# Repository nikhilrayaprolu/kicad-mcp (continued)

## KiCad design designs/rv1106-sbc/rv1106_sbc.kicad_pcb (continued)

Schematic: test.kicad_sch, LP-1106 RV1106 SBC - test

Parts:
TP1: VSYS; TestPoint_Pad_D1.0mm
TP2: 3V3; TestPoint_Pad_D1.0mm
TP3: 1V8; TestPoint_Pad_D1.0mm
TP4: VDDR; TestPoint_Pad_D1.0mm
TP5: 0V9; TestPoint_Pad_D1.0mm
TP6: GND; TestPoint_Pad_D1.0mm
TP7: VBUS; TestPoint_Pad_D1.0mm

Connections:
GND: TP6.1; also elsewhere on the board
VBUS: TP7.1; also elsewhere on the board
VCC_1V8: TP3.1; also elsewhere on the board
VCC_3V3: TP2.1; also elsewhere on the board
VCC_DDR: TP4.1; also elsewhere on the board
VDD_0V9: TP5.1; also elsewhere on the board
VSYS: TP1.1; also elsewhere on the board

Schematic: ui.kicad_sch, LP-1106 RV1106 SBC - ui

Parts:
C57: 1n; C_0402_1005Metric
D3: blue; LED_0603_1608Metric
R22, R23: 100R; R_0402_1005Metric
R24: 10k; R_0402_1005Metric
R28: 1k; R_0402_1005Metric
SW1, SW2: TS-1187A; SW_Push_1P1T_XKB_TS-1187A; MPN TS-1187A-B-A-B; LCSC C318884

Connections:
GND: C57.2, D3.1 (K), SW1.2, SW2.2; also elsewhere on the board
LED_LED_STATUS_A: D3.2 (A), R28.2
LED_STATUS: R28.1; also elsewhere on the board
NPOR: R22.1; also elsewhere on the board
NPOR_BTN: R22.2, SW1.1
RECOVERY: C57.1, R23.1, R24.2; also elsewhere on the board
RECOVERY_BTN: R23.2, SW2.1
VCC_1V8: R24.1; also elsewhere on the board

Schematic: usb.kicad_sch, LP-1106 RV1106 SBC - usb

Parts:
C59: 100n; C_0402_1005Metric
R26: 10k; R_0402_1005Metric
R27: 18k; R_0402_1005Metric

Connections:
GND: C59.2, R27.2; also elsewhere on the board
USB_VBUSDET: C59.1, R26.2, R27.1; also elsewhere on the board
VBUS: R26.1; also elsewhere on the board

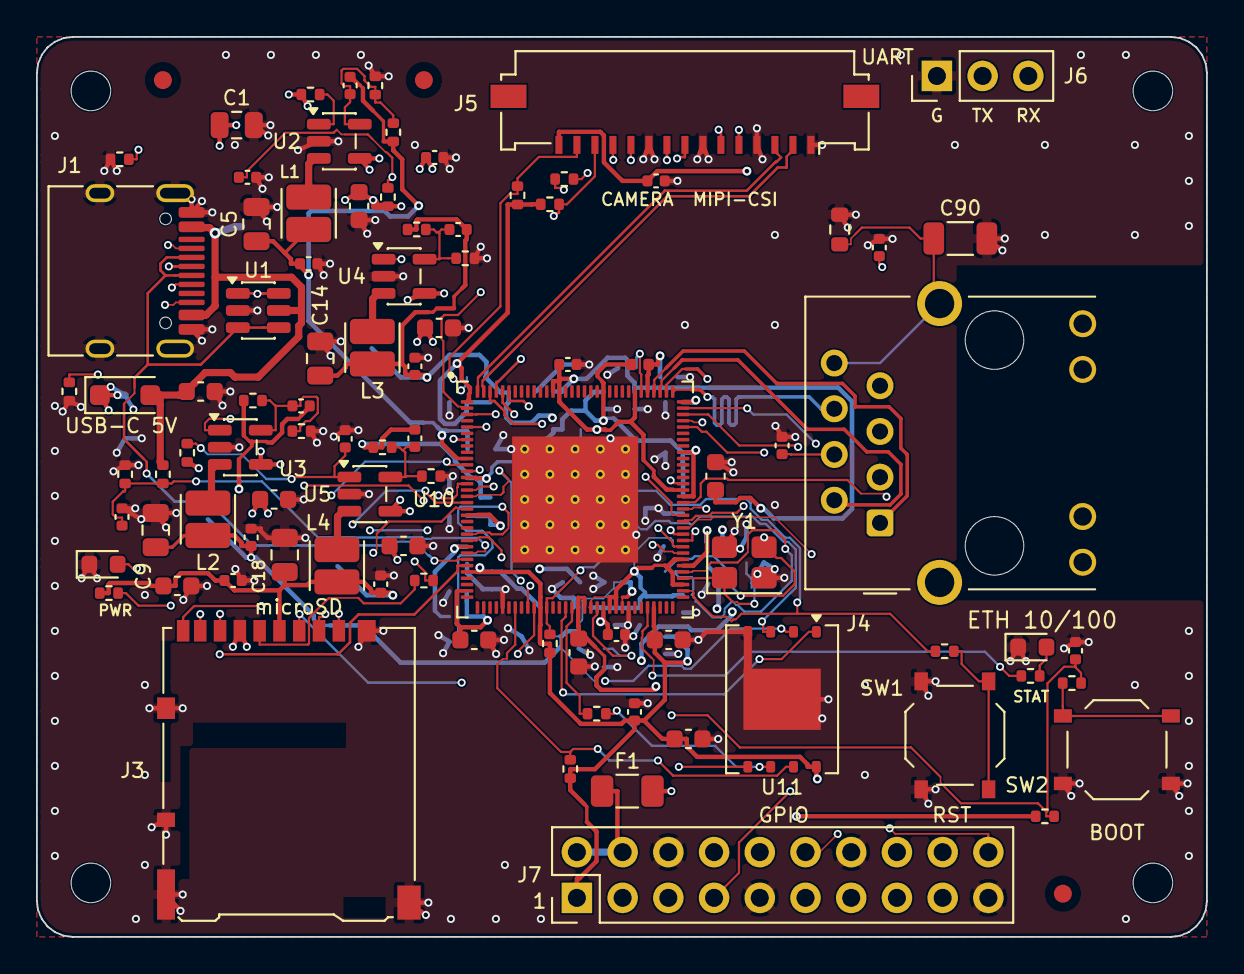
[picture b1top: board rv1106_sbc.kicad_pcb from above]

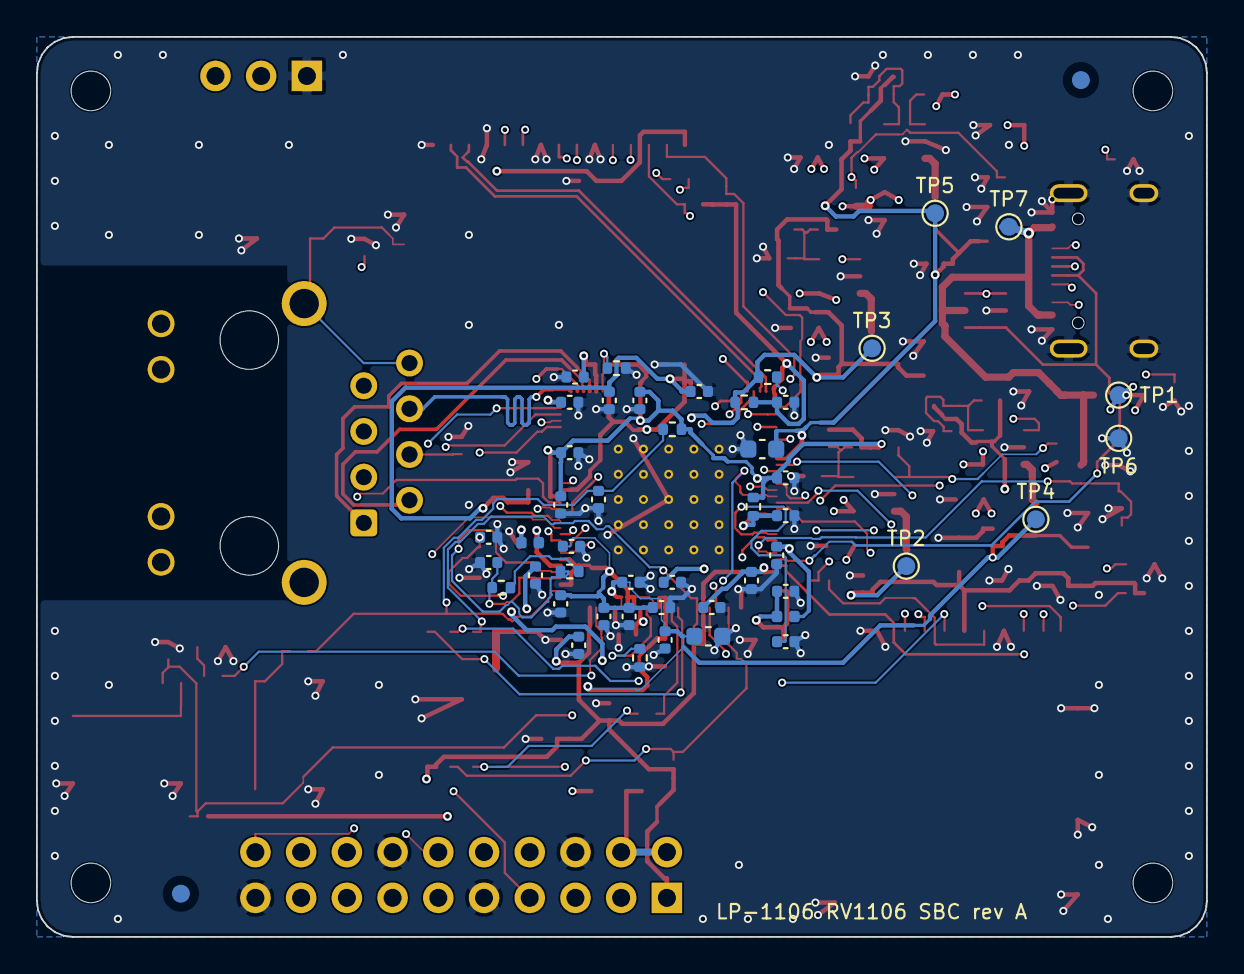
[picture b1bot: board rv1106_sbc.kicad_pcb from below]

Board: 4 copper layers, 65.0 x 50.0 mm, 146 parts (49 on the bottom side), 89 nets.

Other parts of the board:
FID1, FID2, FID3, FID4, FID5: Fiducial; Fiducial_1mm_Mask2mm
H1, H2, H3, H4: MountingHole; MountingHole_2.2mm_M2

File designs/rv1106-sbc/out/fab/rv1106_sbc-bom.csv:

Comment,Designator,Footprint,Quantity,MPN,LCSC Part #
22u/10V,"C1,C14,C18,C5,C9",C_0805_2012Metric,5,,
100n,"C10,C12,C15,C19,C2,C26,C27,C28,C29,C30,C31,C35,C37,C38,C39,C40,C42,C43,C45,C46,C47,C48,C49,C50,C51,C52,C59,C6,C61,C63",C_0402_1005Metric,30,,
1u,"C21,C24,C25,C34,C36,C53,C91",C_0402_1005Metric,7,,
10u,"C22,C23,C32,C33,C41,C44,C60,C62",C_0603_1608Metric,8,,
2.2u/10V,C3,C_0603_1608Metric,1,,
10u/10V,"C13,C17,C4,C8",C_0603_1608Metric,4,,
18p,"C54,C55",C_0402_1005Metric,2,,
10n,"C56,C64,C65",C_0402_1005Metric,3,,
1n,"C57,C58",C_0402_1005Metric,2,,
22p,"C11,C16,C20,C7",C_0402_1005Metric,4,,
1n/2kV,C90,C_1206_3216Metric,1,,
MBR230LSFT1G,D1,D_SOD-123F,1,MBR230LSFT1G,
green,D2,LED_0603_1608Metric,1,,
blue,D3,LED_0603_1608Metric,1,,
0.5A PTC,F1,Fuse_1206_3216Metric,1,SMD1206P050TF,
120R@100MHz,"FB1,FB2,FB3",L_0402_1005Metric,3,BLM15PD121SN1D,
TYPE-C-31-M-12,J1,USB_C_Receptacle_HRO_TYPE-C-31-M-12,1,TYPE-C-31-M-12,C165948
DM3AT-SF-PEJM5,J3,microSD_HC_Hirose_DM3AT-SF-PEJM5,1,DM3AT-SF-PEJM5,
HR911105A,J4,RJ45_Hanrun_HR911105A_Horizontal,1,HR911105A,C12074
FPC 15P 1.0mm,J5,Molex_200528-0150_1x15-1MP_P1.00mm_Horizontal,1,,
DEBUG UART,J6,PinHeader_1x03_P2.54mm_Vertical,1,,
GPIO 2x10,J7,PinHeader_2x10_P2.54mm_Vertical,1,,
1uH,L1,L_Cenker_CKCS252012,1,CKCS252012,
2.2uH,"L2,L3,L4",L_Cenker_CKCS252012,3,CKCS252012,
5.1k,"R1,R2",R_0402_1005Metric,2,,
453k 1%,R11,R_0402_1005Metric,1,,
200k,R13,R_0402_1005Metric,1,,
2.2k,R14,R_0402_1005Metric,1,,
1R,R15,R_0402_1005Metric,1,,
100R,"R16,R22,R23",R_0402_1005Metric,3,,
240R 1%,R17,R_0402_1005Metric,1,,
6.04k 1%,R18,R_0402_1005Metric,1,,
22R,"R19,R29,R32,R34",R_0402_1005Metric,4,,
1M,R20,R_0402_1005Metric,1,,
1k,"R21,R28",R_0402_1005Metric,2,,
18k,R27,R_0402_1005Metric,1,,
49.9k 1%,R3,R_0402_1005Metric,1,,
1M,R33,R_0603_1608Metric,1,,
4.7k,"R35,R36",R_0402_1005Metric,2,,
100k 1%,"R10,R12,R4,R7",R_0402_1005Metric,4,,
10k,"R24,R25,R26,R30,R31,R5",R_0402_1005Metric,6,,
124k 1%,R6,R_0402_1005Metric,1,,
100k,R8,R_0402_1005Metric,1,,
200k 1%,R9,R_0402_1005Metric,1,,
TS-1187A,"SW1,SW2",SW_Push_1P1T_XKB_TS-1187A,2,TS-1187A-B-A-B,C318884
VSYS,TP1,TestPoint_Pad_D1.0mm,1,,
3V3,TP2,TestPoint_Pad_D1.0mm,1,,
1V8,TP3,TestPoint_Pad_D1.0mm,1,,
VDDR,TP4,TestPoint_Pad_D1.0mm,1,,
0V9,TP5,TestPoint_Pad_D1.0mm,1,,
GND,TP6,TestPoint_Pad_D1.0mm,1,,
USBLC6-2SC6,U1,SOT-23-6,1,USBLC6-2SC6,C7519
RV1106G3,U10,QFN-128-1EP_12.3x12.3mm_P0.35mm_EP7x7mm,1,RV1106G3,
W25N01GVZEIG,U11,WSON-8-1EP_8x6mm_P1.27mm_EP3.4x4.3mm,1,W25N01GVZEIG,C111706
TLV62569DBV,"U2,U3,U4,U5",SOT-23-5,4,TLV62569DBVR,C141836
24MHz,Y1,Crystal_SMD_3225-4Pin_3.2x2.5mm,1,,

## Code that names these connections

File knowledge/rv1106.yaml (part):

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      - {pin: 81, name: GPIO1_VCC3V3, range_V: [3.0, 3.465], note: "3.3 V only; VCCIO1 domain (pins 72-80)", reference: "VCC_3V3, C39 100nF", src: "Rockchip_RV1106_Datasheet_V2.2-20260602.pdf#p26; Luckfox-Pico-Pro-Max.pdf#p1"}
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      - {pin: 28, name: USB_AVDD3V3, range_V: [3.0, 3.6], reference: "VCC_3V3 direct, C9 100nF", src: "Rockchip_RV1106_Datasheet_V2.2-20260602.pdf#p26; Luckfox-Pico-Pro-Max.pdf#p1"}
      - {pin: 101, name: ETH_AVDD3V3, range_V: [2.97, 3.63], reference: "net FEPHY_AVDD3V3 = VCC_3V3 via FB1 (UPZ1005D121-1R3TF / BLM15PD121SN1 printed), C8 100nF", src: "Rockchip_RV1106_Datasheet_V2.2-20260602.pdf#p26; Luckfox-Pico-Pro-Max.pdf#p1 @230-254,526-538"}
      - {pin: 13, name: GPIO4_VCC, range_V_3v3: [3.0, 3.465], range_V_1v8: [1.62, 1.98], note: "VCCIO4 = SDMMC0 domain (pins 11,12,14-18)", reference: "VCC_3V3, C41 100nF", src: "Rockchip_RV1106_Datasheet_V2.2-20260602.pdf#p26; Luckfox-Pico-Pro-Max.pdf#p1"}
      - {pin: 43, name: GPIO3_VCC, note: "VCCIO3 = EMMC/FSPI domain (pins 38-42,44-48)", reference: "net VCCIO_FLASH = VCC_3V3, C40 100nF (+C42 10uF/C43 100nF at flash)", src: "Rockchip_RV1106_Datasheet_V2.2-20260602.pdf#p26; Luckfox-Pico-Pro-Max.pdf#p1"}
      - {pin: 88, name: GPIO6_VCC, note: "VCCIO6 domain (pins 83-87,89-95)", reference: "VCC_3V3", src: "Rockchip_RV1106_Datasheet_V2.2-20260602.pdf#p26; Luckfox-Pico-Pro-Max.pdf#p1"}
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      Luckfox SCH labels the VDD_0V9 buck "Setp 1" (EN pulled up with 10K, no cap -> starts first); VCC_DDR and VCC_1V8 share
      enable net VCC_DDR_1V8_EN with 200K/100nF RC delay (Ultra-W labels this block "VCC_DDR--->VCC_1V8 Setp 2");
      VCC_3V3 EN via 200K/100nF from PWR_EN. Practical order: 0.9 V -> 1.35 V/1.8 V -> 3.3 V.
    reset: "nPOR (pin 66) pulled up to VCC_3V3 by R12 1K with C38 10nF to GND (RC power-on reset); reset key Key1 via R22 100R."
    src: "Luckfox-Pico-Pro-Max.pdf#p1 @222-556,6-64; Luckfox-Pico-Ultra-W.pdf#p1 @585-745,205-305; Luckfox-Pico-Pro-Max.pdf#p1 @445-535,180-230"
    unverified: true    # Rockchip's own sequencing rule is in the (non-public here) hardware design guide

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    reference: "Y2 32.768 kHz passive crystal 2012; C33 18pF, C34 18pF C0G. Optional (RTC)."
    src: "Luckfox-Pico-Pro-Max.pdf#p1 @388-412,161-177"
  reset:
    pins: {nPOR: 66}                                # src: Rockchip_RV1106_Datasheet_V2.2-20260602.pdf#p21
    reference: "Active-low. R12 1K pull-up to VCC_3V3, C38 10nF to GND; Key1 to GND via R22 100R; ED1 ESD (NC/ESD5451N)."
    src: "Luckfox-Pico-Pro-Max.pdf#p1 @406,224 (R12/C38) and @530-622,400-440 (Key1)"
  recovery_maskrom:
    pins: {SARADC_IN0: 23}
    reference: >-
      Net RECOVERY on SARADC_IN0 (pin 23): R21 10K pull-up to VCC_1V8, C44 1nF to GND, Key2 ("RECOVERY Key") to GND via
      R23 100R (ED2 ESD NC). Holding it low at power-up is the BOOT/recovery button.
    behaviour: >-
      Rockchip convention: SARADC_IN0 low at boot -> loader/maskrom (USB download via rkdeveloptool/upgrade_tool on USB OTG).
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    src: "Luckfox-Pico-Pro-Max.pdf#p1 @445-535,365-440; Rockchip_RV1106_Datasheet_V2.2-20260602.pdf#p7"
    unverified: true
  fspi_spi_nand:
    pins: {FSPI_CLK: 48, FSPI_CS0: 47, FSPI_D0: 41, FSPI_D1: 42, FSPI_D2: 44, FSPI_D3: 39}   # src: Rockchip_RV1106_Datasheet_V2.2-20260602.pdf#p22
    io_domain: "VCCIO3 = pin 43 GPIO3_VCC (VCCIO_FLASH = 3.3 V in reference)"
    reference: >-
      U2 Winbond W25N02KVZEIR (2Gb SPI NAND, WSON-8 + EPAD): pin1 /CS=FSPI_CS0N, 2 DO(IO1)=FSPI_D1, 3 /WP(IO2)=FSPI_D2,
      4 VSS, 5 DI(IO0)=FSPI_D0, 6 CLK=FSPI_CLK, 7 /HOLD(IO3)=FSPI_D3, 8 VCC=VCCIO_FLASH, 9 EPAD=GND.
      FSPI_CLK has R15 22R series resistor at the SoC. R18 10K pull-up on FSPI_D2, R19 10K pull-up on FSPI_D3 (to VCCIO_FLASH).
      VCCIO_FLASH decoupling C42 10uF + C43 100nF.
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    conflict: "Pins 12/14 are also UART2_TX_M0/UART2_RX_M0, so the debug console uses UART2_M1 instead."
    src: "Rockchip_RV1106_Datasheet_V2.2-20260602.pdf#p21; Luckfox-Pico-Pro-Max.pdf#p1 @445-622,440-505 and @540-622,195-240"
  usb2_otg:
    pins: {USB_DP: 27, USB_DM: 26, USB_VBUSDET: 25}   # src: Rockchip_RV1106_Datasheet_V2.2-20260602.pdf#p22
    supplies: {USB_AVDD3V3: 28, SARADC_USB_AVDD1V8: 24}
    id_pin: "None on QFN128 (no USB_ID in DS Table 2-1); host/device role is set in software."
    external_resistors: "None on the QFN part: there is no USB reference-resistor pin."
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  uart2_debug_console:
    pins: {UART2_TX_M1: 79, UART2_RX_M1: 80}         # GPIO1_B2 / GPIO1_B3; src: Rockchip_RV1106_Datasheet_V2.2-20260602.pdf#p21
    io_domain: "VCCIO1 (3.3 V only)"
    reference: "Pins 79/80 -> nets UART2_TX/UART2_RX -> header GP00/GP01 (U3 40-pin). Luckfox Linux console is UART2_M1, 115200 8N1."
    src: "Rockchip_RV1106_Datasheet_V2.2-20260602.pdf#p21; Luckfox-Pico-Pro-Max.pdf#p1 @222-395,62-118 and @325-385,190-262"
    console_baud_unverified: true
  saradc:
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  required_external_resistors_summary:
    - {pin: 102, name: ETH_EXTR, value: "6.04K 1% to GND", src: "Luckfox-Pico-Pro-Max.pdf#p1"}
    - {pin: 52, name: DRAM_ZQ, value: "240R 1% to GND", src: "Luckfox-Pico-Pro-Max.pdf#p1"}
    - {pin: 66, name: nPOR, value: "1K pull-up to 3V3 + 10nF to GND", src: "Luckfox-Pico-Pro-Max.pdf#p1"}
    - {pin: 23, name: SARADC_IN0, value: "10K pull-up to 1V8 + 1nF (recovery key)", src: "Luckfox-Pico-Pro-Max.pdf#p1"}
    - {pins: [68, 69], name: OSC, value: "1M across XIN/XOUT, 22R series on XOUT, 2x18pF", src: "Luckfox-Pico-Pro-Max.pdf#p1"}
  datasheet_name_quirks:
    - {pin: 110, note: "DS prints 'SDMMC_D0/I2S0_LRCK/...'; by analogy with pins 109/111-114 this is SDMMC1_D0_M0 (SCH shows SDIO_D0_M0).", src: "Rockchip_RV1106_Datasheet_V2.2-20260602.pdf#p22; Luckfox-Pico-Pro-Max.pdf#p1", unverified: true}
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  - {ref: U5, part: unknown, role: "buck 5V -> VCC_1V8, 1.0uH", src: "Luckfox-Pico-Pro-Max.pdf#p1", unverified: true}
  - {ref: U7, part: unknown, role: "buck 5V -> VCC_DDR 1.35V, 1.0uH", src: "Luckfox-Pico-Pro-Max.pdf#p1", unverified: true}
  - {ref: U6, part: unknown, role: "buck 5V -> VCC_3V3 with BST cap, 2.2uH, FB 0.8V", src: "Luckfox-Pico-Pro-Max.pdf#p1", unverified: true}
  - {ref: U3, part: "40-pin header (Pico/RP2040-style GP00..GP28, VBUS, VSYS, 3V3_En, 3V3_Out, Vref, RUN=NPOR)", role: "IO header", src: "Luckfox-Pico-Pro-Max.pdf#p1 @222-395,62-118"}
  - {ref: D1, part: MBR230LSFT1G, role: "VBUS -> VSYS Schottky", src: "Luckfox-Pico-Pro-Max.pdf#p1"}
  - {ref: "D2, D3", part: B5819WS, role: "RTC supply diode-OR", src: "Luckfox-Pico-Pro-Max.pdf#p1"}
  - {ref: Q1, part: SI2301CDS-T1-E3, role: "microSD power switch (P-MOSFET)", src: "Luckfox-Pico-Pro-Max.pdf#p1"}
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  36: {name: "CODEC_MIC1P", type: analog, src: "Rockchip_RV1106_Datasheet_V2.2-20260602.pdf#p22"}
  37: {name: "CODEC_AVSS", type: ground, src: "Rockchip_RV1106_Datasheet_V2.2-20260602.pdf#p22"}
  38: {name: "EMMC_D5/SPI1_CLK_M0/UART1_RX_M2/I2C2_SCL_M1/GPIO4_A7_u", type: io, gpio: "GPIO4_A7", default_pull: "up", io_domain: "VCCIO3 (pin43 GPIO3_VCC, 1.8V/3.3V)", src: "Rockchip_RV1106_Datasheet_V2.2-20260602.pdf#p22"}
  39: {name: "EMMC_D3/FSPI_D3/GPIO4_A6_u", type: io, gpio: "GPIO4_A6", default_pull: "up", io_domain: "VCCIO3 (pin43 GPIO3_VCC, 1.8V/3.3V)", src: "Rockchip_RV1106_Datasheet_V2.2-20260602.pdf#p22"}
  40: {name: "EMMC_D4/SPI1_CS0_M0/UART1_TX_M2/I2C2_SDA_M1/GPIO4_A5_u", type: io, gpio: "GPIO4_A5", default_pull: "up", io_domain: "VCCIO3 (pin43 GPIO3_VCC, 1.8V/3.3V)", src: "Rockchip_RV1106_Datasheet_V2.2-20260602.pdf#p22"}
  41: {name: "EMMC_D0/FSPI_D0/GPIO4_A4_u", type: io, gpio: "GPIO4_A4", default_pull: "up", io_domain: "VCCIO3 (pin43 GPIO3_VCC, 1.8V/3.3V)", src: "Rockchip_RV1106_Datasheet_V2.2-20260602.pdf#p22"}
  42: {name: "EMMC_D1/FSPI_D1/GPIO4_A3_u", type: io, gpio: "GPIO4_A3", default_pull: "up", io_domain: "VCCIO3 (pin43 GPIO3_VCC, 1.8V/3.3V)", src: "Rockchip_RV1106_Datasheet_V2.2-20260602.pdf#p22"}
  43: {name: "GPIO3_VCC", type: power_in, src: "Rockchip_RV1106_Datasheet_V2.2-20260602.pdf#p22"}
  44: {name: "EMMC_D2/FSPI_D2/GPIO4_A2_u", type: io, gpio: "GPIO4_A2", default_pull: "up", io_domain: "VCCIO3 (pin43 GPIO3_VCC, 1.8V/3.3V)", src: "Rockchip_RV1106_Datasheet_V2.2-20260602.pdf#p22"}
  45: {name: "EMMC_D6/SPI1_MOSI_M0/UART0_TX_M2/I2C0_SCL_M1/GPIO4_A1_u", type: io, gpio: "GPIO4_A1", default_pull: "up", io_domain: "VCCIO3 (pin43 GPIO3_VCC, 1.8V/3.3V)", src: "Rockchip_RV1106_Datasheet_V2.2-20260602.pdf#p22"}
  46: {name: "EMMC_D7/SPI1_MISO_M0/UART0_RX_M2/I2C0_SDA_M1/GPIO4_A0_u", type: io, gpio: "GPIO4_A0", default_pull: "up", io_domain: "VCCIO3 (pin43 GPIO3_VCC, 1.8V/3.3V)", src: "Rockchip_RV1106_Datasheet_V2.2-20260602.pdf#p22"}
  47: {name: "EMMC_CMD/FSPI_CS0/GPIO4_B0_u", type: io, gpio: "GPIO4_B0", default_pull: "up", io_domain: "VCCIO3 (pin43 GPIO3_VCC, 1.8V/3.3V)", src: "Rockchip_RV1106_Datasheet_V2.2-20260602.pdf#p22"}
  48: {name: "EMMC_CLK/FSPI_CLK/GPIO4_B1_d", type: io, gpio: "GPIO4_B1", default_pull: "down", io_domain: "VCCIO3 (pin43 GPIO3_VCC, 1.8V/3.3V)", src: "Rockchip_RV1106_Datasheet_V2.2-20260602.pdf#p22"}
  49: {name: "DDR_VDDQ_1", type: power_in, src: "Rockchip_RV1106_Datasheet_V2.2-20260602.pdf#p22"}
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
